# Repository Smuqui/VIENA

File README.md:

# Fiat Elettra
This is a temporary repo for a project being developed at [Instituto Superior Técnico](https://tecnico.ulisboa.pt/pt/).
The goal of the project is to convert an old Fiat Elettra car to be autonumous
driven and be a possible investigation platform for further projects.

## submodules documentation:
1. [maxon Epos 70/10](http://maxon-epos.readthedocs.io/en/latest/index.html)
2. [Novatel OEM4](http://novatel-oem4-python.readthedocs.io/en/latest/)

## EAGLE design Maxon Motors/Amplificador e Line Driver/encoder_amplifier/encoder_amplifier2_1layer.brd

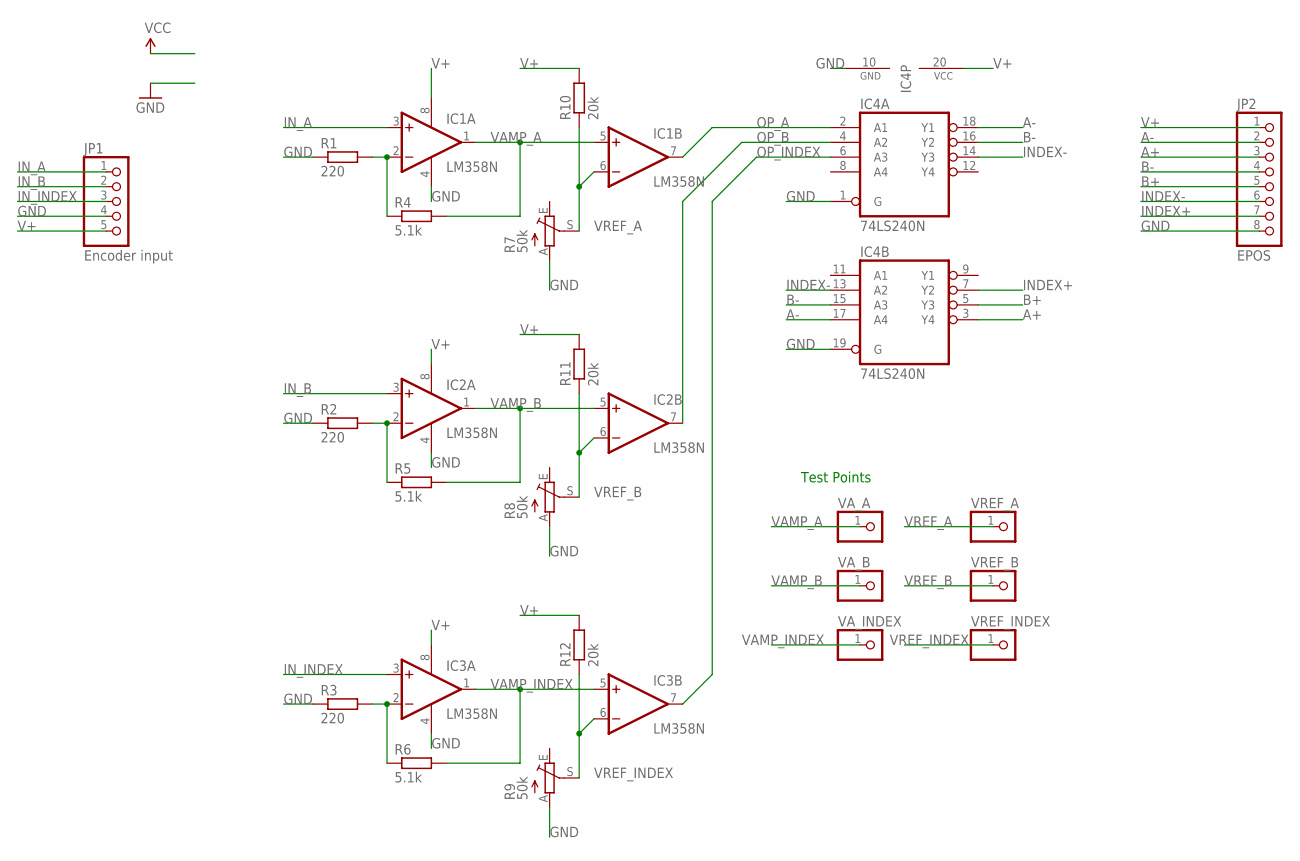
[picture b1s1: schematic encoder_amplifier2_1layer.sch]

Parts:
IC1, IC2, IC3: LM358N; DIL08
IC4: 74LS240N; DIL20
JP1: Encoder input; 1X05
JP2: EPOS; 1X08
R1, R2, R3: 220; 0204/7
R4, R5, R6: 5.1k; 0204/7
R7, R8, R9: 50k; LI15
R10, R11, R12: 20k; 0204/7
VA_A: PINHD-1X1; 1X01
VA_B: PINHD-1X1; 1X01
VA_INDEX: PINHD-1X1; 1X01
VREF_A: PINHD-1X1; 1X01
VREF_B: PINHD-1X1; 1X01
VREF_INDEX: PINHD-1X1; 1X01

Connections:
A+: IC4.3 (Y4), JP2.3
A-: IC4.17 (A4), IC4.18 (Y1), JP2.2
B+: IC4.5 (Y3), JP2.5
B-: IC4.15 (A3), IC4.16 (Y2), JP2.4
GND: IC1.4 (V-), IC2.4 (V-), IC3.4 (V-), IC4.1 (G), IC4.10 (GND), IC4.19 (G), JP1.4, JP2.8, R1.1, R2.1, R3.1, R7.A, R8.A, R9.A
INDEX+: IC4.7 (Y2), JP2.7
INDEX-: IC4.13 (A2), IC4.14 (Y3), JP2.6
IN_A: IC1.3 (+IN), JP1.1
IN_B: IC2.3 (+IN), JP1.2
IN_INDEX: IC3.3 (+IN), JP1.3
unnamed: IC1.2 (-IN), R1.2, R4.1
unnamed: IC2.2 (-IN), R2.2, R5.1
unnamed: IC3.2 (-IN), R3.2, R6.1
OP_A: IC1.7 (OUT), IC4.2 (A1)
OP_B: IC2.7 (OUT), IC4.4 (A2)
OP_INDEX: IC3.7 (OUT), IC4.6 (A3)
V+: IC1.8 (V+), IC2.8 (V+), IC3.8 (V+), IC4.20 (VCC), JP1.5, JP2.1, R10.2, R11.2, R12.2
VAMP_A: IC1.1 (OUT), IC1.5 (+IN), R4.2, VA_A.1
VAMP_B: IC2.1 (OUT), IC2.5 (+IN), R5.2, VA_B.1
VAMP_INDEX: IC3.1 (OUT), IC3.5 (+IN), R6.2, VA_INDEX.1
VREF_A: IC1.6 (-IN), R7.S, R10.1, VREF_A.1
VREF_B: IC2.6 (-IN), R8.S, R11.1, VREF_B.1
VREF_INDEX: IC3.6 (-IN), R9.S, R12.1, VREF_INDEX.1

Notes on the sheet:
Test Points

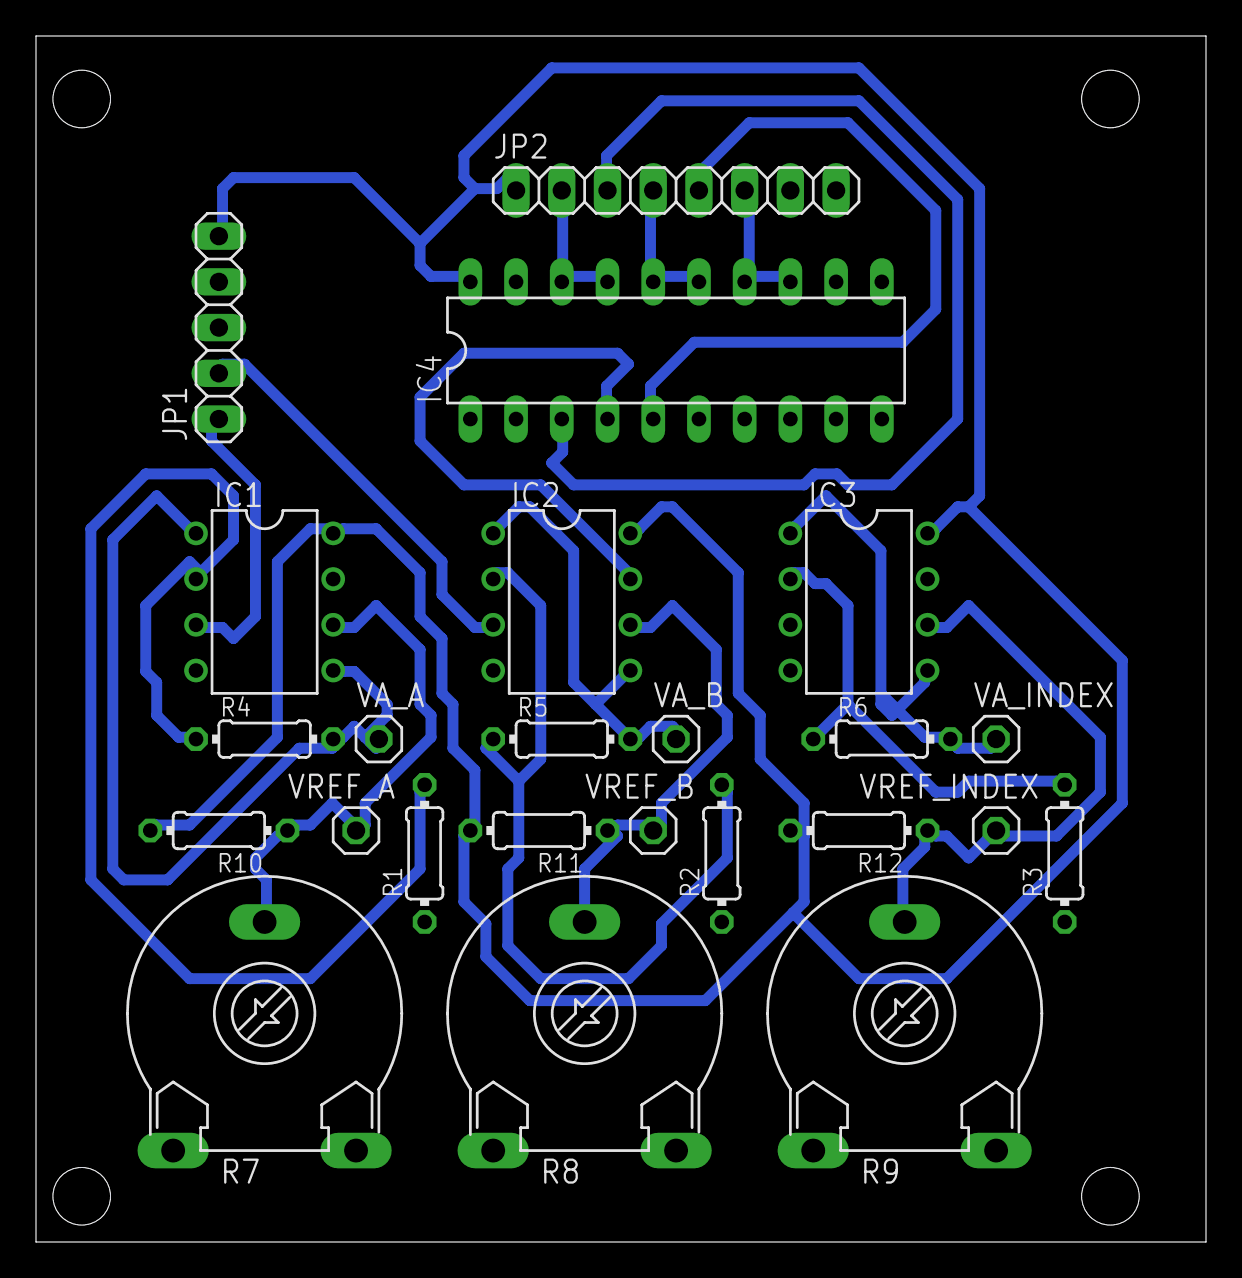
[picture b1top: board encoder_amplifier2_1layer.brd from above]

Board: 2 copper layers, 65.0 x 67.0 mm, 24 parts (0 on the bottom side), 23 nets.

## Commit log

2016-07-04 initial upload
2016-07-04 deleted duplicated documentation
2016-09-07 Added EPOS matlab draft lib class
    work in progress
2016-09-07 minor update
    Added license at header.
    Changed comments to support possible doxygen generatiron documentation.
2016-09-07 updated documentation. Improved changeState
2016-09-08 removed docs, add new functions to Epos lib. Minor corrections
2016-09-12 added new functions to Epos Lib
    added Eagle project for Encoder amplifier
2016-09-13 added Current and Velocity related gains functions
2016-09-14 added a few functions
2016-09-19 improved epos lib class
    added preliminary example GUI
2016-09-27 improved examples. Needed to be tested. Work in progress...
2016-09-30 fixed bug in setPositionControlParam
2016-10-21 Added a working progress positionMode GUI.
    example positionMode GUI. (work in progress).
    Corrected a bug in sensor configuration.
    Start Changing docs for reST markup
2016-12-29 removed gps folder
2016-12-29 moved gps as a separated project
2016-12-29 added position encoder files
2016-12-30 corrected setSensorConfig, updated positionModeGUI
2017-02-08 Added store function. Improved GUI for handle angle of steering wheel
    Also a lot of changes in documentation of functions to move to sphinx in future.
2017-02-09 Changed to bitset to improve performance. Finished comments sections
2017-02-13 Moving Epos library to a separete repository
2017-02-13 added submodule for EPOS
2017-02-20 adicionado testes e resumo com o volante e epos
2017-02-21 Updated submodule Maxon-Epos
2017-02-21 Updated README.md
    minor typos
2017-05-10 moved test folders to a single dir
2017-10-08 added razorIMU interface for python
2017-12-10 Updated submodule razorIMU_python
2018-08-16 Major rearrangement of struture
2018-08-16 Major restructure to keep up with various modules.
2018-08-16 added battery development
2018-08-21 added submodule for documentation
2018-09-26 updated to latest documentation submodule
2018-11-04 updated to latest submodules
2018-11-15 Updated submodule Documentation/Latex
2018-11-15 Updated submodule VIENA-Interface
2018-11-15 Updated submodule battery/VIENA_battery
2018-11-15 Updated submodule mqtt-controller-dev
2019-01-03 Updated submodule mqtt-controller
2019-01-03 Updated submodule EPOS_Canopen
2019-01-03 Updated submodule logger-AHRS
2019-01-03 Updated submodule novatel_OEM4_python
2019-03-07 uploaded a few Matlab classes for simulation of the car movement
2019-03-07 added example tester
2019-05-07 Updated submodule Matlab/@CreateMap
2019-05-07 Updated submodule Matlab/@SteeringController

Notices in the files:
parts and their libraries:
SparkFun-Aesthetics: Licensing: Creative Commons ShareAlike 4.0 International - https://creativecommons.org/licenses/by-sa/4.0
